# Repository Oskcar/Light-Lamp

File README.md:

# Light-Lamp
codes, sketches... etc

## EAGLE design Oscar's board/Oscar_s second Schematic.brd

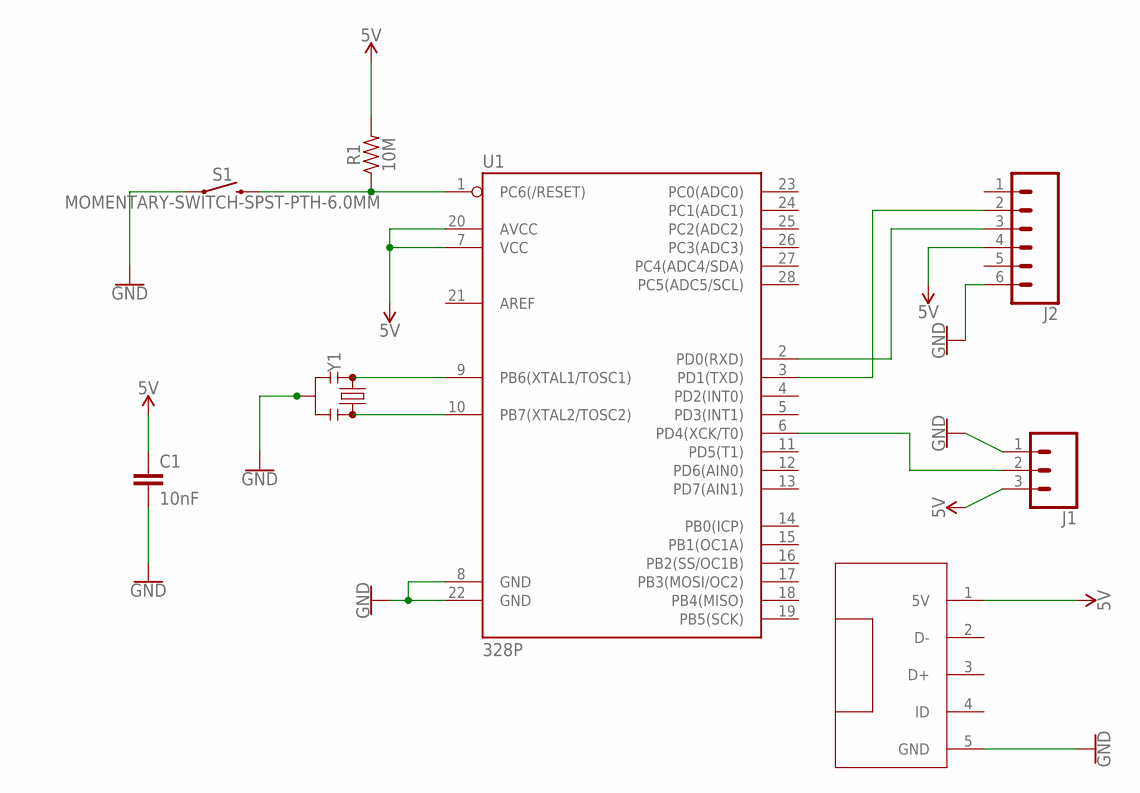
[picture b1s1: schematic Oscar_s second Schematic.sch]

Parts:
C1: 10nF; CAP-PTH-10MM
J1: CONN_03; 1X03
J2: CONN_06SILK_FEMALE_PTH; 1X06
R1: 10M; AXIAL-0.3
S1: MOMENTARY-SWITCH-SPST-PTH-6.0MM; TACTILE_SWITCH_PTH_6.0MM
U1: 328P; DIP28
U$1: USB
Y1: RESONATORPTH-7.6X3.8; RESONATOR-PTH-7.6X3.8

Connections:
5V: C1.1, J1.3, J2.4, R1.P$2 (2), U1.7 (VCC), U1.20 (AVCC), U$1.1 (5V)
GND: C1.2, J1.1, J2.6, S1.1, U1.8 (GND), U1.22 (GND), U$1.5 (GND), Y1.2
unnamed: R1.P$1 (1), S1.3 (2), U1.1 (PC6(/RESET))
unnamed: J2.3, U1.2 (PD0(RXD))
unnamed: U1.9 (PB6(XTAL1/TOSC1)), Y1.1
unnamed: U1.10 (PB7(XTAL2/TOSC2)), Y1.3
unnamed: J2.2, U1.3 (PD1(TXD))
unnamed: J1.2, U1.6 (PD4(XCK/T0))

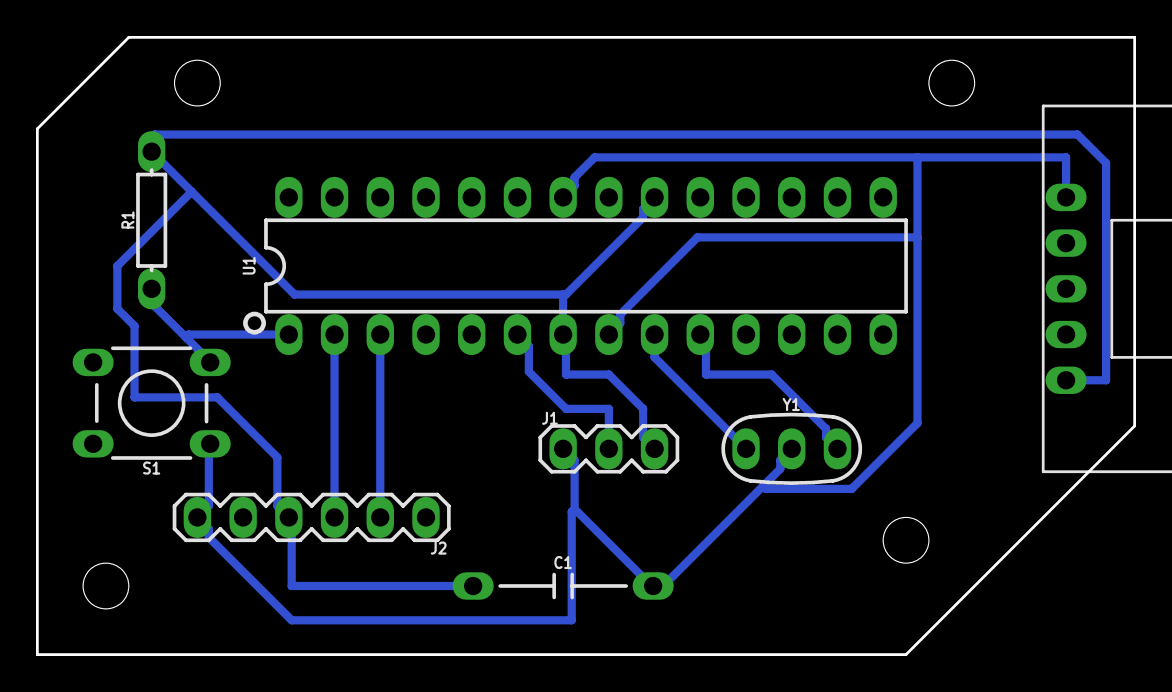
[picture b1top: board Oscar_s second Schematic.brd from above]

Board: 2 copper layers, 61.0 x 34.3 mm, 8 parts (0 on the bottom side), 8 nets.

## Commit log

2019-01-22 I added all of my files and codes to Git
2019-02-13 Arduino Code
2019-02-13 Cost Sheet

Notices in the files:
parts and their libraries:
SparkFun-PowerSymbols: Licensing: Creative Commons ShareAlike 4.0 International - https://creativecommons.org/licenses/by-sa/4.0
